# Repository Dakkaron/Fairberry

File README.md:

# Fairberry

The goal of this project is to add a BlackBerry Q10 keyboard to non-BlackBerry phones. While this can easily be adapted to suit any other phone with an USB port at the bottom, I will focus on releasing files for the Fairphone 4, since that is what I have. Feel free to adjust it to your phone and share your results in the discussion area.

The Fairberry keyboard is detachable and can be used without any modifications on the phone. Since it connects over USB, there is no need for separate batteries or glitchy Bluetooth connections.

## What can you expect?

### Demo video

## How to build it?

Recommended: [Custom mainboard](https://github.com/Dakkaron/Fairberry/blob/main/Documentation/Hardware_Fairberry_Mainboard.md)

[Old Arduino-based hardware](https://github.com/Dakkaron/Fairberry/blob/main/Documentation/Hardware_Arduinobased.md)

## How to use it?

[Key combinations and apps](https://github.com/Dakkaron/Fairberry/blob/main/Documentation/UX_Shortcuts_and_Apps.md)

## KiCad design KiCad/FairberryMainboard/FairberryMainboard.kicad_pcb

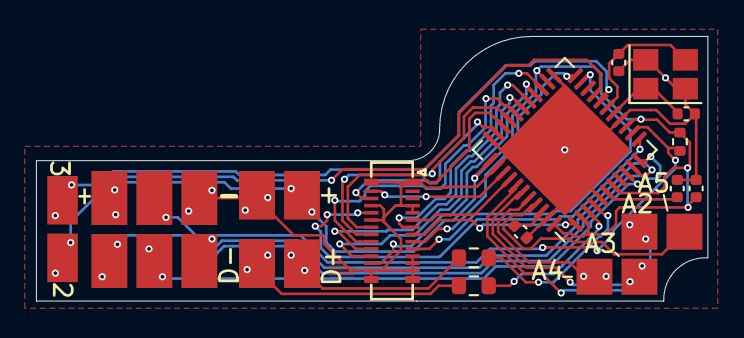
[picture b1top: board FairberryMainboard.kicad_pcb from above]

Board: 2 copper layers, 37.3 x 14.7 mm, 13 parts (0 on the bottom side), 28 nets.

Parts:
C1: 1uF; C_0402_1005Metric
C2, C3: 0.1uF; C_0402_1005Metric
C4, C5: 22pF; C_0402_1005Metric
J1: USB_Header; TestPoint_Pad_2x2_2.0x3.0mm
J2: Conn_02x03_Odd_Even; TestPoint_Pad_2x3_2.0x3.0mm
R1: 10K; R_0402_1005Metric
R2, R3: 22; R_0603_1608Metric
U1: ATmega32U4-MU; QFN-44-1EP_7x7mm_P0.5mm_EP5.2x5.2mm
U2: BBQ10KBD; BM14B(0.8)-24DS-0.4V(53)
Y1: Crystal_GND24; Crystal_SMD_SeikoEpson_FA238-4Pin_3.2x2.5mm

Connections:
/USB_Plug_D+: J1.4, R2.2
/USB_Plug_D-: J1.3, R3.2
/USB_UC_D+: R2.1, U1.4 (D+)
/USB_UC_D-: R3.1, U1.3 (D-)
GND: C1.2, C2.2, C3.2, C4.2, C5.2, J1.1, J2.6, U1.5 (UGND), U1.15 (GND), U1.23 (GND), U1.33 (~HWB/PE2), U1.35 (GND), U1.43 (GND), U1.45 (GND), U2.1 (GND), U2.4 (AGND), U2.5 (GND), U2.11 (GND), U2.12 (GND), U2.13 (GND), U2.14 (GND), U2.15 (GND), U2.16 (GND), U2.23 (LEDK_2_3), U2.25 (LEDK_1_4), U2.28 (GND), Y1.2, Y1.4
unnamed: C1.1, U1.6 (UCAP)
unnamed: C3.1, U1.42 (AREF)
unnamed: C4.1, U1.16 (XTAL2), Y1.1
unnamed: C5.1, U1.17 (XTAL1), Y1.3
unnamed: J2.1, U1.11 (PB3)
unnamed: J2.3, U1.9 (PB1)
unnamed: J2.4, U1.10 (PB2)
unnamed: J2.5, R1.2, U1.13 (~RESET)
unnamed: U1.1 (PE6), U2.8 (ROW2)
unnamed: U1.12 (PB7), U2.24 (LEDA_3_4)
unnamed: U1.21 (PD3), U2.10 (COL3)
unnamed: U1.22 (PD5), U2.9 (COL2)
unnamed: U1.25 (PD4), U2.7 (COL1)
unnamed: U1.26 (PD6), U2.17 (COL4)
unnamed: U1.27 (PD7), U2.19 (COL5)
unnamed: U1.28 (PB4), U2.18 (ROW3)
unnamed: U1.29 (PB5), U2.20 (ROW4)
unnamed: U1.30 (PB6), U2.21 (ROW5)
unnamed: U1.31 (PC6), U2.22 (ROW6)
unnamed: U1.32 (PC7), U2.26 (LEDA_1_2)
unnamed: U1.36 (PF7), U2.27 (ROW7)
unnamed: U1.37 (PF6), U2.6 (ROW1)
VCC: C2.1, J1.2, J2.2, R1.1, U1.2 (UVCC), U1.7 (VBUS), U1.14 (VCC), U1.24 (AVCC), U1.34 (VCC), U1.44 (AVCC)

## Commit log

2022-01-27 Fixing a comment
2022-01-27 added images
2022-01-27 First part of the readme
2022-01-27 Case files
2022-01-27 Readme and USB connection diagram
2022-01-27 Small fix in the cases
2022-01-27 Changed to Keyboard.h (instead of KeyboardDE.h) due to a bug in Android 11 which makes other layouts useless if you have any accessibility app active.
2022-01-27 Updated documentation
2022-02-01 Corrected small error in README
    a Blackberry Pro Micro - > an Arduino Pro Micro
2022-02-01 Update README.md
    +verb
2022-02-02 Update README.md
    Formatting fix
2022-05-04 Fixed power management
2022-05-07 Added blinking backlight when in cursor mode
2022-05-07 Moved case files to Fairphone4 subfolder
2022-05-07 Flat inline case
2022-05-08 Changed Row 7 pin from 3 to A2 to free up the I2C port for possible future expansion
2022-05-09 Better powersaving options and documentation
2022-05-09 Removed serial output mode
2022-05-09 Powersaving improvements
2022-05-16 Added Hirose connector footprint
2022-05-16 Added Hirose connector footprint with shorter URL for JLCPCB
2022-08-30 Many improvements to the firmware source code, including support for different boards and a separate config file
2022-08-30 Fairberry v0.1.1 mainboard
2022-08-30 .gitignore
2022-08-30 OpenSCAD-based script to generate the phone case parametrically
2022-10-07 Mainboard pinout graphics
2022-10-07 Sticky keys and debounce
2022-10-07 Bugfix for sticky keys and reduced debug output
2022-10-09 Only one key is sticky at a time
2022-10-09 Sticky keys and debouncing options in configuration.h
2022-10-09 Resetting sticky keys on idle and on entering/exiting cursor mode
2022-10-09 Fixed sticky sym + ctrl -> '0'
2022-10-09 No sticky keys while brightness is changed
2022-10-09 Fixed sticky SYM + ALT -> TAB
2022-10-10 Kicad files for mainboard v0.2.0
2022-10-10 Tidying up
2022-10-10 Documentation
2022-10-10 Documetation
2022-10-10 Images for the documentation
2022-10-10 Added v0.2.0 compatibility
2022-10-10 Moved documentation of Arduino version into it's own file
2022-10-10 Moved build manual out of Readme.md
2022-10-10 Formatting
2022-10-12 Added assembly guide
2022-10-12 Added license (CC NC-SA 4.0)
2022-11-27 FastNoKeyPressed: initial implementation
2023-01-18 Fixed debouncing
2023-03-28 Added new title picture
2023-03-28 Changed title image
2023-09-08 Fixed POWERSAVE_ARDUINO_POWERDOWN
2024-02-14 Split backlight into two zones, removed status LEDs, reduced y size by 1mm
2024-02-22 Finished v0.3.0
2024-02-22 Made firmware compatible with v0.3.0 (doesn't make use of dual backlight controls yet), refactoring
2024-03-22 Improved Case Generator script, added presets for Fairphone 4 and Samsung Galaxy A54
2024-03-22 Refactoring and bugfixes for the firmware
2024-03-22 Firmware refactoring
2024-03-22 Presets and refactoring for the generator script
2024-03-22 Finalisation of v0.3.0 PCB
2024-03-22 License/Version header for firmware
2024-03-22 Removed generated stl
2024-03-22 Hardware revision v0.3.0 (#16)
    * Split backlight into two zones, removed status LEDs, reduced y size by 1mm
    * Made firmware compatible with v0.3.0 (doesn't make use of dual backlight controls yet), refactoring
    * Improved Case Generator script, added presets for Fairphone 4 and Samsung Galaxy A54
    * Finalisation of v0.3.0 PCB
    * License/Version header for firmware
    * Removed generated stl
2024-03-22 Small fix for Samsung A54 dummy
2024-03-22 Hardware revision v0.3.0 (#16) (#19)
    * Split backlight into two zones, removed status LEDs, reduced y size by 1mm
    * Made firmware compatible with v0.3.0 (doesn't make use of dual backlight controls yet), refactoring
    * Improved Case Generator script, added presets for Fairphone 4 and Samsung Galaxy A54
    * Finalisation of v0.3.0 PCB
    * License/Version header for firmware
    * Removed generated stl
2024-03-22 Images for v0.3.0 documentation
2024-03-23 Added frontpage image
2024-03-23 Added new image to README.md
2024-03-24 Fixing keyActive/keyPressed related bugs
2024-03-26 Partially working initial version
2024-03-28 Buffer improvements

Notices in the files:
KiCad/FairberryMainboard/FairberryMainboard.kicad_pcb:
©Dakkaron, 2024
